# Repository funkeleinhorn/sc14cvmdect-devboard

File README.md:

# SC14CVMDECT Devboard

Open Hardware devboard for the [SC14CVMDECT](https://www.renesas.com/en/products/wireless-connectivity/dect/sc14cvmdect-cordless-voice-module) module from Renesas.
Documentation of the devboard and the existing Open Source Software implementations for the SC14CVMDECT module can be found at [redected.org](https://redected.org).

This project is licensed as open hardware. See LICENSE.txt for details.

## Images

Here you can see how the PCB looks:

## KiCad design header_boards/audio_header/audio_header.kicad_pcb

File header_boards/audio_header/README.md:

# SC14CVMDECT Devboard Audio Header

Header board providing audio circutry for the Open Hardware devboard for the [SC14CVMDECT](https://www.renesas.com/en/products/wireless-connectivity/dect/sc14cvmdect-cordless-voice-module) module from Renesas.
Documentation of the devboard and the header boards can be found at [redected.org](https://redected.org).

This project is licensed as open hardware. See LICENSE.txt for details.

## Images

Here you can see how the PCB looks:

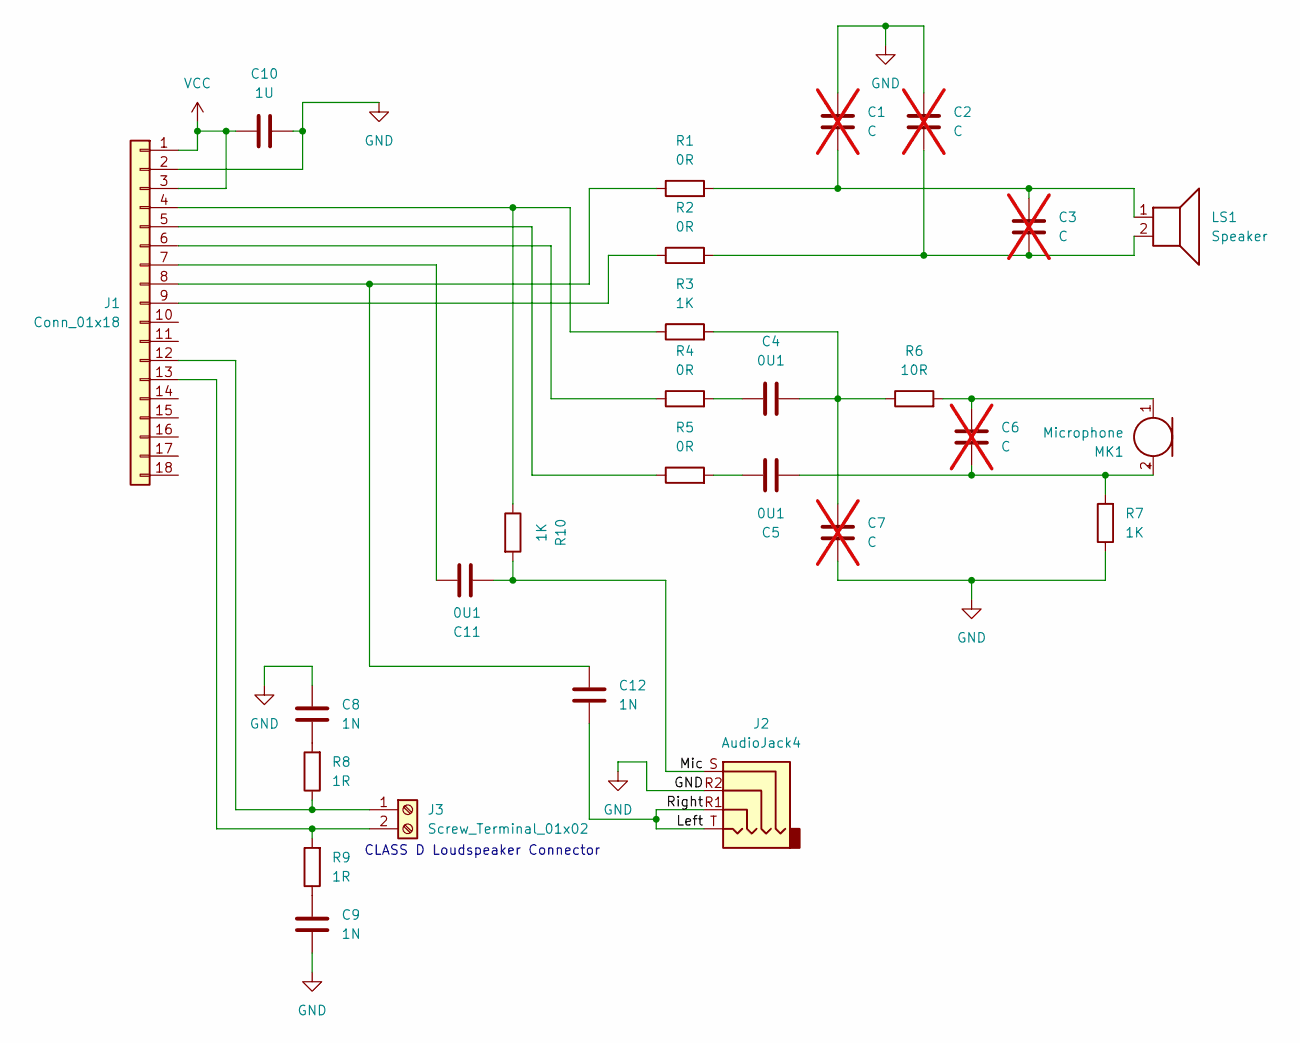
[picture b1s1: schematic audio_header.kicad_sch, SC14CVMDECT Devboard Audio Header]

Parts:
C1, C2, C3, C6, C7: C; C_0603_1608Metric; not fitted
C4, C5, C11: 0U1; C_0603_1608Metric
C8, C9, C12: 1N; C_0603_1608Metric
C10: 1U; C_0603_1608Metric
J1: Conn_01x18; PinSocket_1x18_P2.54mm_Vertical
J2: AudioJack4; Jack_3.5mm_CUI_SJ-4351X-SMT_Horizontal
J3: Screw_Terminal_01x02; TerminalBlock_MaiXu_MX126-5.0-02P_1x02_P5.00mm
LS1: Speaker; Speaker_CUI_CMR-15062S-67
MK1: Microphone; CUI_CMC-4013-SMT
R1, R2, R4, R5: 0R; R_0603_1608Metric
R3, R7, R10: 1K; R_0603_1608Metric
R6: 10R; R_0603_1608Metric
R8, R9: 1R; R_0603_1608Metric

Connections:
/Left: C12.1, J2.R1, J2.T
/Mic: C11.2, J2.S, R10.2
GND: C1.1, C2.1, C7.2, C8.2, C9.1, C10.2, J1.2, J2.R2, R7.1
unnamed: C1.2, C3.1, LS1.1, R1.2
unnamed: C2.2, C3.2, LS1.2, R2.2
unnamed: C4.1, R4.2
unnamed: C4.2, C7.1, R3.2, R6.1
unnamed: C5.1, R5.2
unnamed: C8.1, R8.2
unnamed: C9.2, R9.1
unnamed: J1.4, R3.1, R10.1
unnamed: J1.5, R5.1
unnamed: J1.6, R4.1
unnamed: C11.1, J1.7
unnamed: C12.2, J1.8, R1.1
unnamed: J1.9, R2.1
unnamed: J1.12, J3.1, R8.1
unnamed: J1.13, J3.2, R9.2
unnamed: C5.2, C6.2, MK1.2 (+), R7.2
unnamed: C6.1, MK1.1 (-), R6.2
VCC: C10.1, J1.1, J1.3

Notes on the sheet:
CLASS D Loudspeaker Connector

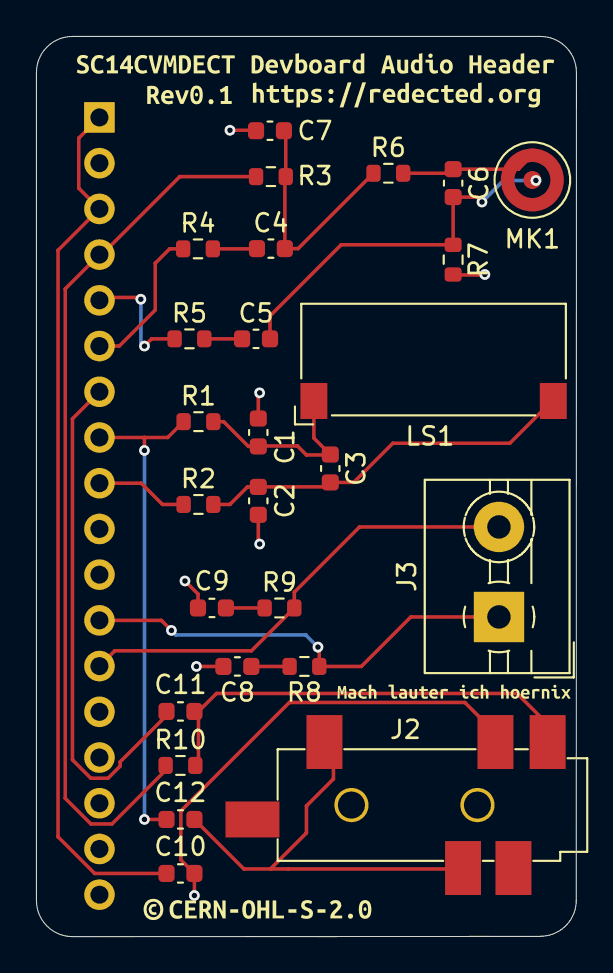
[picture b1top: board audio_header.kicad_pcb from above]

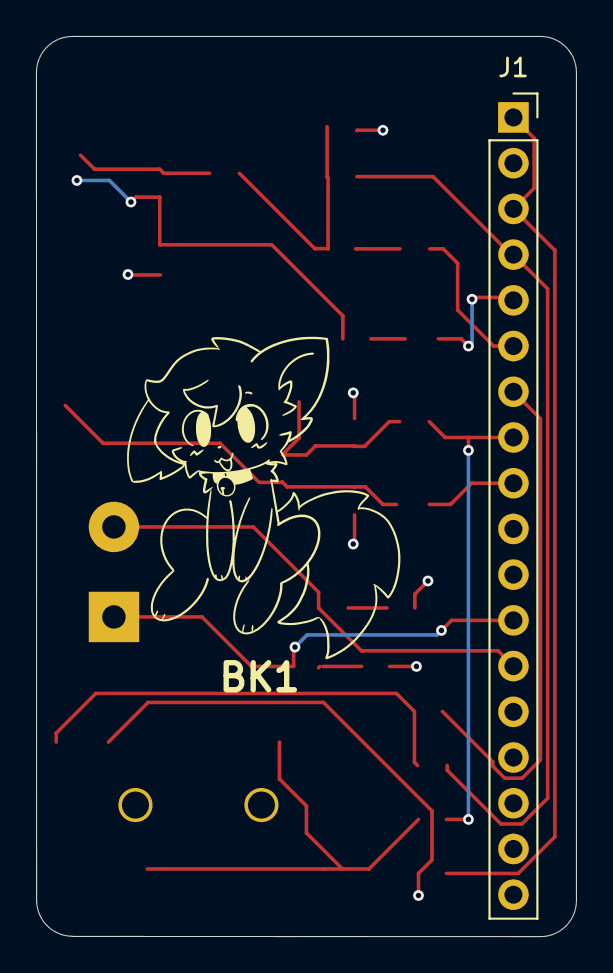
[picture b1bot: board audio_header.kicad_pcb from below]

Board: 4 copper layers, 30.0 x 50.0 mm, 34 parts (2 on the bottom side), 21 nets.

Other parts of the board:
BK1: LOGO
kibuzzard-67A72E30: G***; kibuzzard-67A72E30
kibuzzard-67A72F6B: G***; kibuzzard-67A72F6B
kibuzzard-67A72F64: G***; kibuzzard-67A72F64
kibuzzard-67A72F83: G***; kibuzzard-67A72F83
kibuzzard-67A7302E: G***; kibuzzard-67A7302E
kibuzzard-67ACE384: G***; kibuzzard-67ACE384

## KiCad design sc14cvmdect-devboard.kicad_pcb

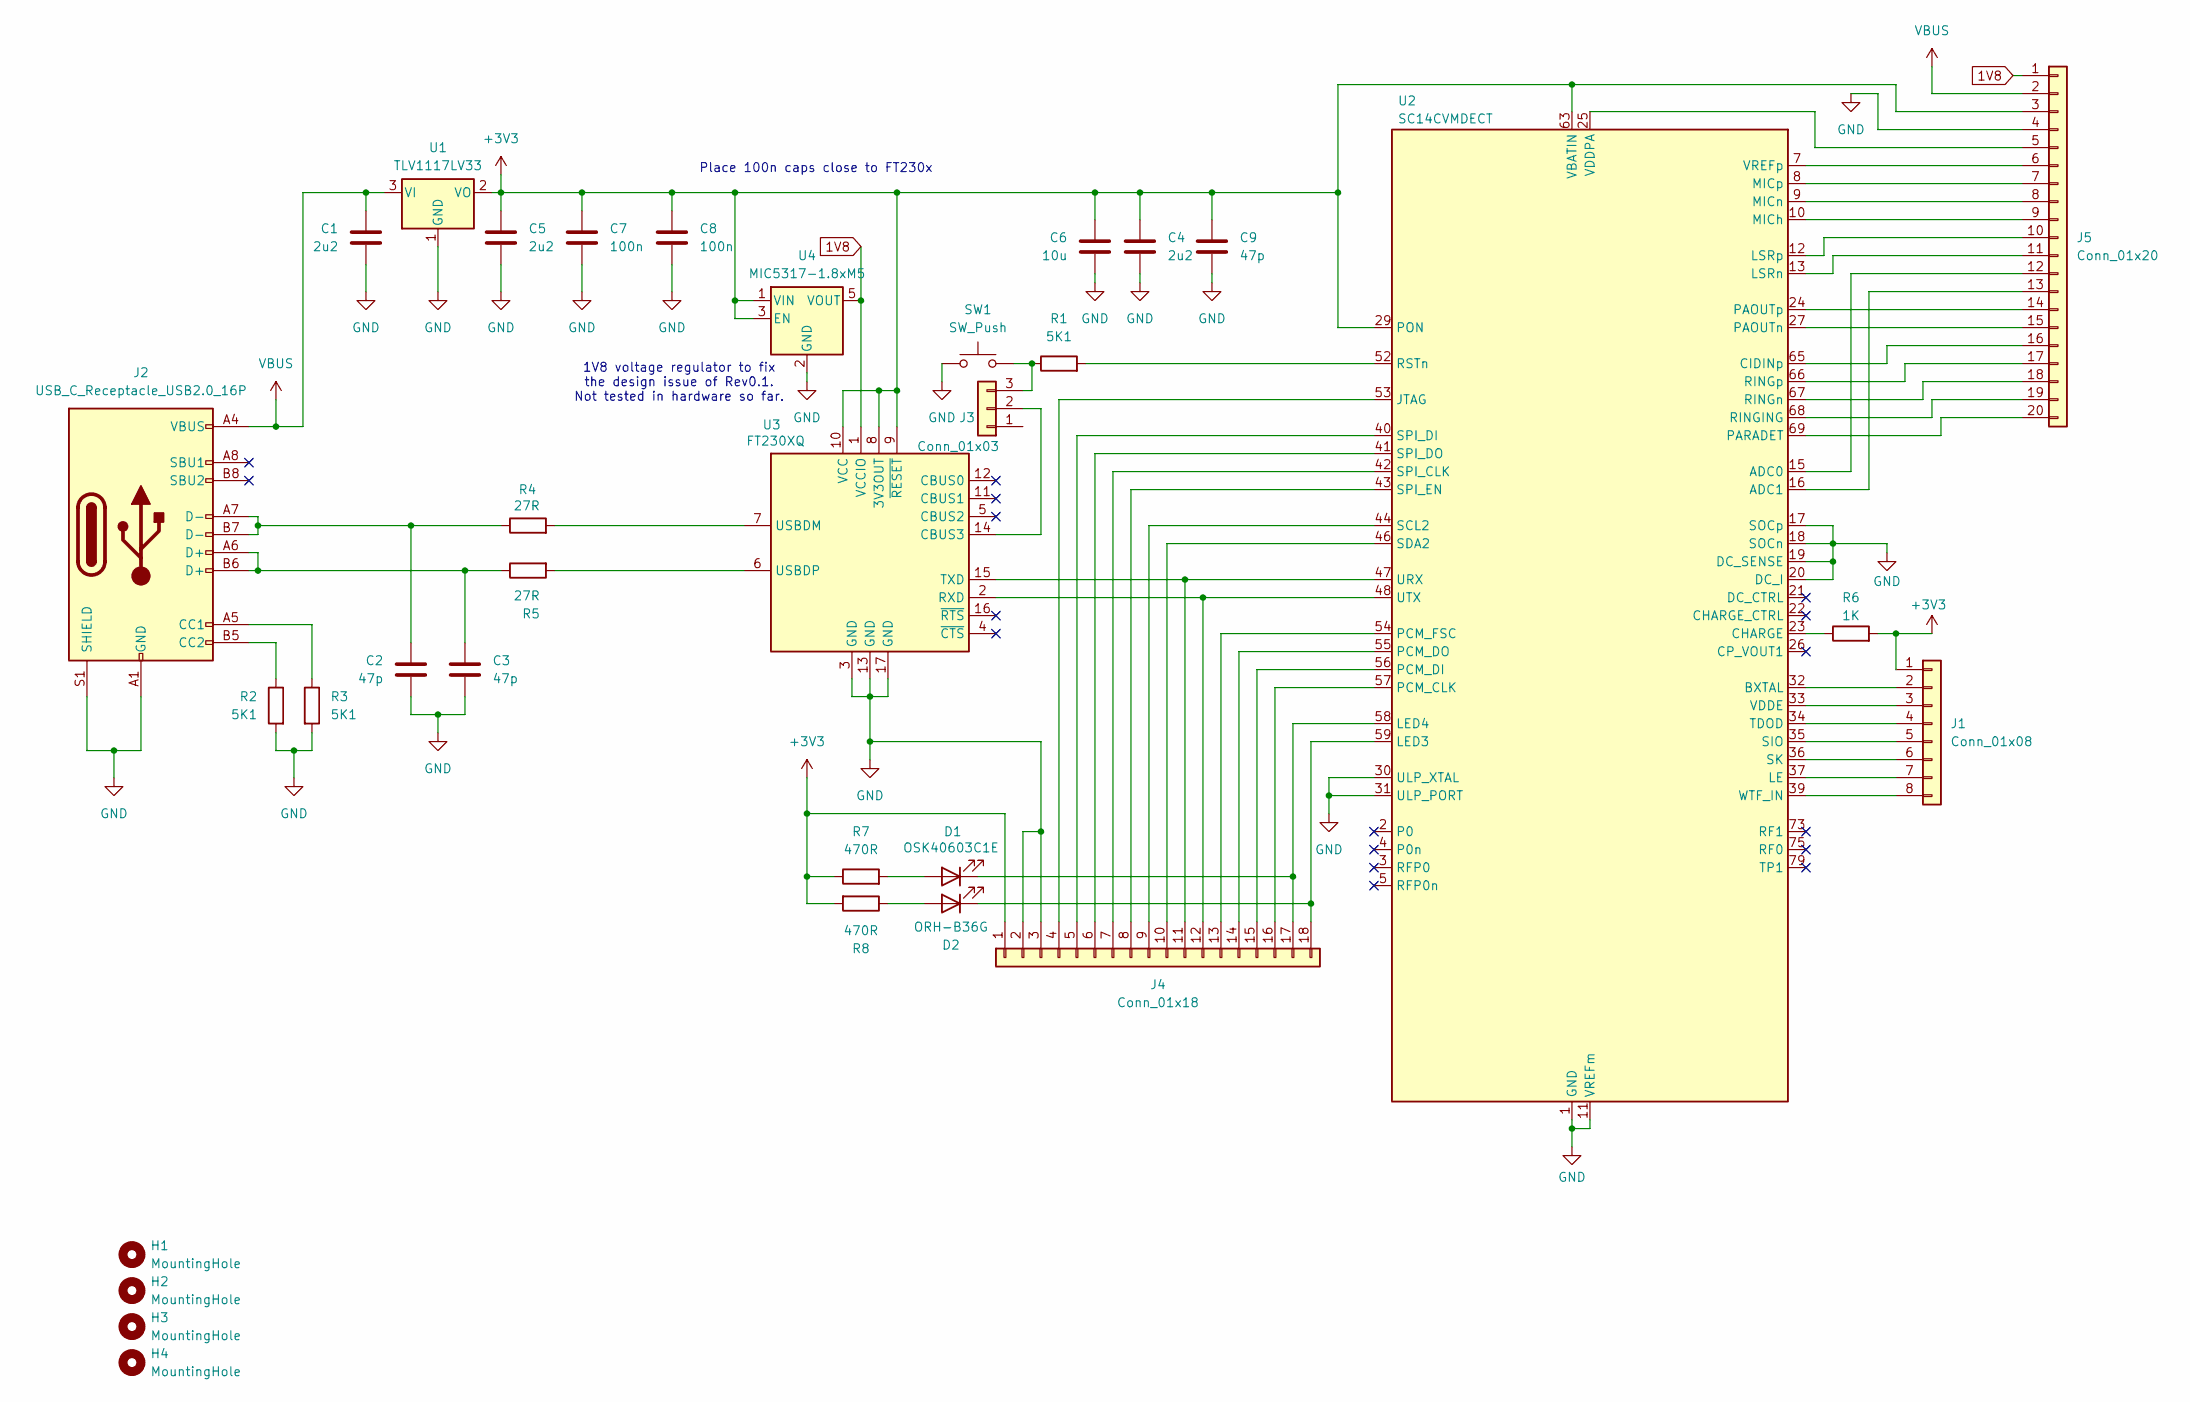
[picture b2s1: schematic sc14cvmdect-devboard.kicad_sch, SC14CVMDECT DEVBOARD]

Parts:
C1, C4, C5: 2u2; C_0805_2012Metric
C2, C3, C9: 47p; C_0603_1608Metric
C6: 10u; C_0805_2012Metric
C7, C8: 100n; C_0603_1608Metric
D1: OSK40603C1E; LED_0603_1608Metric
D2: ORH-B36G; LED_0603_1608Metric
H1, H2, H3, H4: MountingHole; MountingHole_3.2mm_M3_DIN965
J1: Conn_01x08; PinHeader_1x08_P2.54mm_Vertical
J2: USB_C_Receptacle_USB2.0_16P; USB_C_Receptacle_JAE_DX07S016JA1R1500
J3: Conn_01x03; PinHeader_1x03_P2.54mm_Vertical
J4: Conn_01x18; PinHeader_1x18_P2.54mm_Vertical
J5: Conn_01x20; PinHeader_1x20_P2.54mm_Vertical
R1, R2, R3: 5K1; R_0603_1608Metric
R4, R5: 27R; R_0603_1608Metric
R6: 1K; R_0603_1608Metric
R7, R8: 470R; R_0603_1608Metric
SW1: SW_Push; SW_SPST_PTS647_Sx70
U1: TLV1117LV33; SOT-223-3_TabPin2
U2: SC14CVMDECT
U3: FT230XQ; QFN-16-1EP_4x4mm_P0.65mm_EP2.1x2.1mm
U4: MIC5317-1.8xM5; SOT-23-5

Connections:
1V8: J5.1, U3.1 (VCCIO), U4.5 (VOUT)
+3V3: C4.1, C5.1, C6.1, C7.1, C8.1, C9.1, J1.1, J4.1, J5.3, R6.2, R7.1, R8.2, U1.2 (VO), U2.29 (PON), U2.63 (VBATIN), U2.64 (VBATIN), U3.8 (3V3OUT), U3.9 (~RESET), U3.10 (VCC), U4.1 (VIN), U4.3 (EN)
GND: C1.2, C2.2, C3.2, C4.2, C5.2, C6.2, C7.2, C8.2, C9.2, J2.A1 (GND), J2.A12 (GND), J2.B1 (GND), J2.B12 (GND), J2.S1 (SHIELD), J4.2, J4.3, J5.4, R2.2, R3.2, SW1.1, U1.1 (GND), U2.1 (GND), U2.6 (GND), U2.11 (VREFm), U2.14 (GND), U2.17 (SOCp), U2.18 (SOCn), U2.19 (DC_SENSE), U2.20 (DC_I), U2.28 (GND), U2.30 (ULP_XTAL), U2.31 (ULP_PORT), U2.38 (GND), U2.45 (GND), U2.49 (GND), U2.50 (GND), U2.51 (GND), U2.60 (GND), U2.70 (GND), U2.71 (GND), U2.72 (GND), U2.74 (GND), U2.76 (GND), U2.77 (GND), U2.78 (GND), U2.80 (GND), U3.3 (GND), U3.13 (GND), U3.17 (GND), U4.2 (GND)
unnamed: C2.1, J2.A7 (D-), J2.B7 (D-), R4.1
unnamed: C3.1, J2.A6 (D+), J2.B6 (D+), R5.1
unnamed: D1.2 (A), R7.2
unnamed: D1.1 (K), J4.17, U2.58 (LED4)
unnamed: D2.2 (A), R8.1
unnamed: D2.1 (K), J4.18, U2.59 (LED3)
unnamed: J1.2, U2.32 (BXTAL)
unnamed: J1.3, U2.33 (VDDE)
unnamed: J1.4, U2.34 (TDOD)
unnamed: J1.5, U2.35 (SIO)
unnamed: J1.6, U2.36 (SK)
unnamed: J1.7, U2.37 (LE)
unnamed: J1.8, U2.39 (WTF_IN)
unnamed: J2.A5 (CC1), R3.1
unnamed: J2.B5 (CC2), R2.1
unnamed: J3.2, U3.14 (CBUS3)
unnamed: J3.3, R1.1, SW1.2
unnamed: J4.4, U2.53 (JTAG)
unnamed: J4.5, U2.40 (SPI_DI)
unnamed: J4.6, U2.41 (SPI_DO)
unnamed: J4.7, U2.42 (SPI_CLK)
unnamed: J4.8, U2.43 (SPI_EN)
unnamed: J4.9, U2.44 (SCL2)
unnamed: J4.10, U2.46 (SDA2)
unnamed: J4.11, U2.47 (URX), U3.15 (TXD)
unnamed: J4.12, U2.48 (UTX), U3.2 (RXD)
unnamed: J4.13, U2.54 (PCM_FSC)
unnamed: J4.14, U2.55 (PCM_DO)
unnamed: J4.15, U2.56 (PCM_DI)
unnamed: J4.16, U2.57 (PCM_CLK)
unnamed: J5.5, U2.25 (VDDPA)
unnamed: J5.6, U2.7 (VREFp)
unnamed: J5.7, U2.8 (MICp)
unnamed: J5.8, U2.9 (MICn)
unnamed: J5.9, U2.10 (MICh)
unnamed: J5.10, U2.12 (LSRp)
unnamed: J5.11, U2.13 (LSRn)
unnamed: J5.12, U2.15 (ADC0)
unnamed: J5.13, U2.16 (ADC1)
unnamed: J5.14, U2.24 (PAOUTp)
unnamed: J5.15, U2.27 (PAOUTn)
unnamed: J5.16, U2.65 (CIDINp)
unnamed: J5.17, U2.66 (RINGp)
unnamed: J5.18, U2.67 (RINGn)
unnamed: J5.19, U2.68 (RINGING)
unnamed: J5.20, U2.69 (PARADET)
unnamed: R6.1, U2.23 (CHARGE)
unnamed: R1.2, U2.52 (RSTn)
unnamed: R4.2, U3.7 (USBDM)
unnamed: R5.2, U3.6 (USBDP)
VBUS: C1.1, J2.A4 (VBUS), J2.A9 (VBUS), J2.B4 (VBUS), J2.B9 (VBUS), J5.2, U1.3 (VI)

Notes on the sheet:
Place 100n caps close to FT230x
1V8 voltage regulator to fix the design issue of Rev0.1. Not tested in hardware so far.

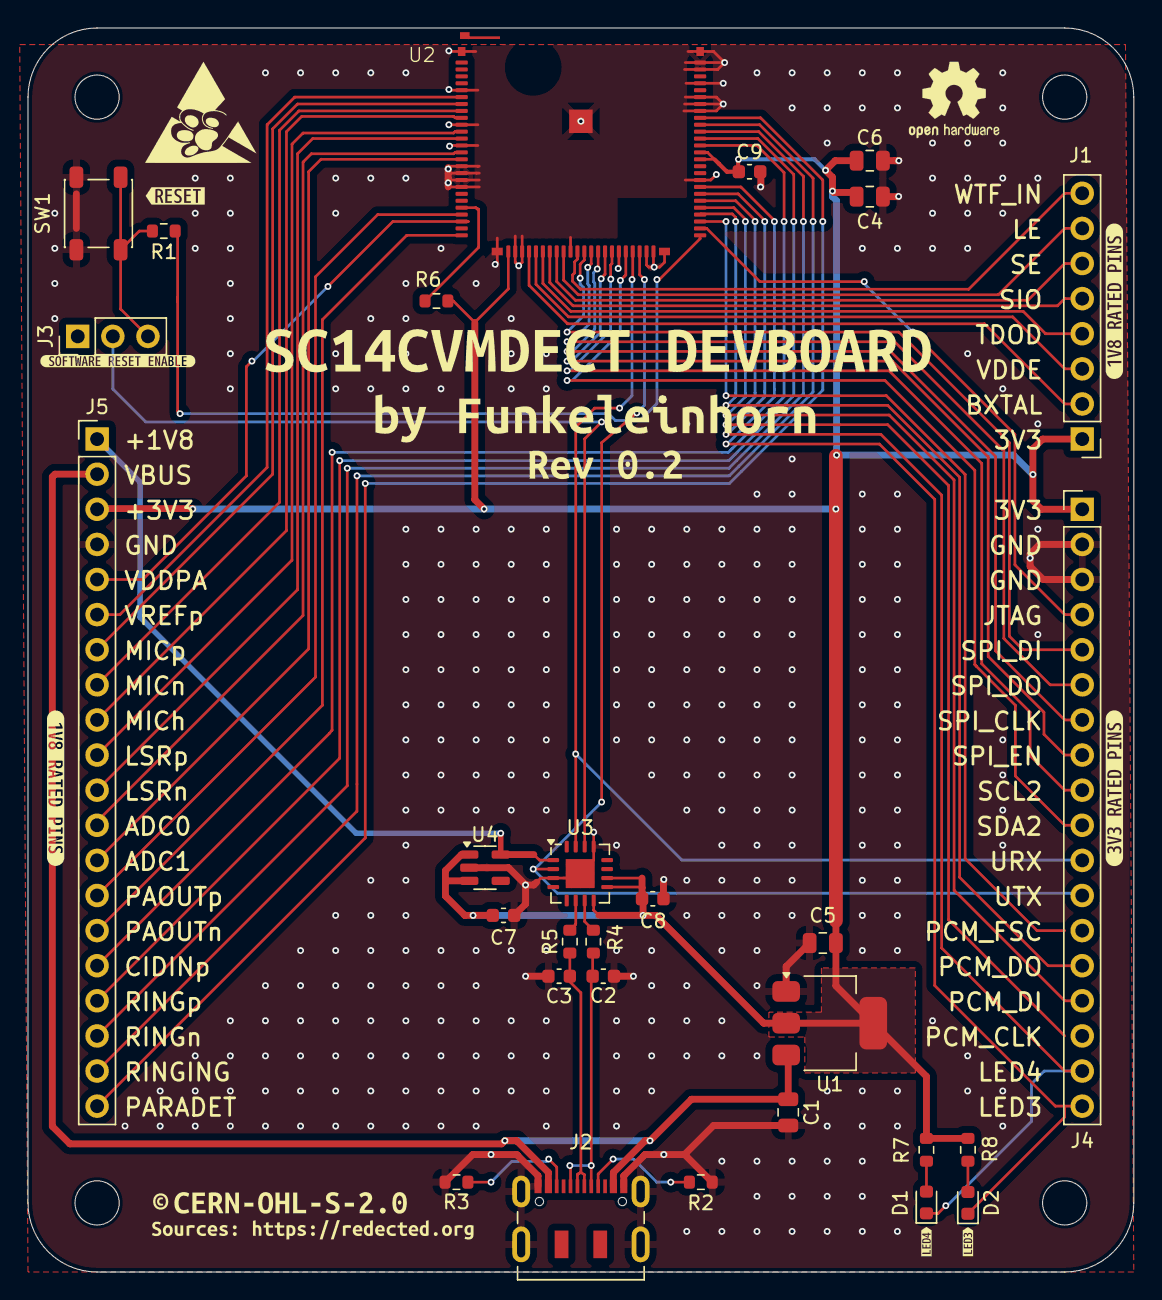
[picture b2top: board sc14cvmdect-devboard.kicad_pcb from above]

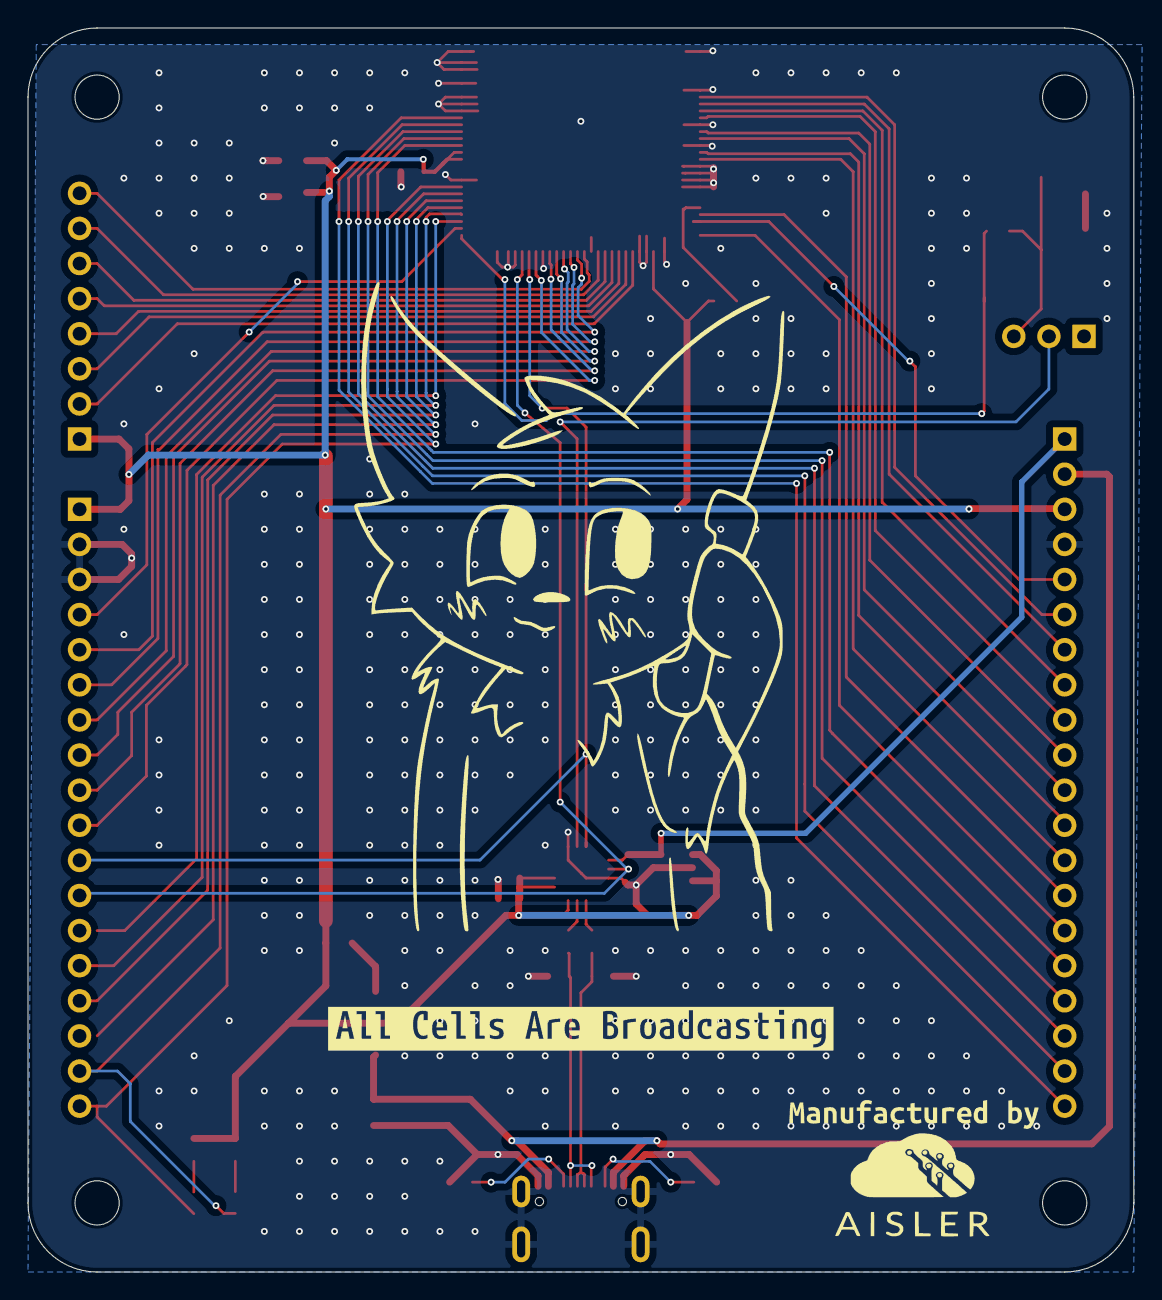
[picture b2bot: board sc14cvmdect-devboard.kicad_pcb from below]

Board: 4 copper layers, 80.0 x 90.0 mm, 48 parts (2 on the bottom side), 54 nets.

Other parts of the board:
kibuzzard-676BF11C: G***; kibuzzard-676BF11C
kibuzzard-67575DB5: G***; kibuzzard-67575DB5
kibuzzard-67575EB8: G***; kibuzzard-67575EB8
kibuzzard-67575F62: G***; kibuzzard-67575F62
kibuzzard-67575F78: G***; kibuzzard-67575F78
kibuzzard-67576AD7: G***; kibuzzard-67576AD7
kibuzzard-67576C4F: G***; kibuzzard-67576C4F
kibuzzard-67576C6D: G***; kibuzzard-67576C6D
kibuzzard-67576C73: G***; kibuzzard-67576C73
kibuzzard-67576CB2: G***; kibuzzard-67576CB2
kibuzzard-675753CF: G***; kibuzzard-675753CF
kibuzzard-675756D3: G***; kibuzzard-675756D3
kibuzzard-675758CB: G***; kibuzzard-675758CB
kibuzzard-67575390: G***; kibuzzard-67575390
kibuzzard-67575747: G***; kibuzzard-67575747

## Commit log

2024-12-20 Revision 0.1
    The initial revision of the SC14CVMDECT devboard.
    15 boards of this revision were manufactured for and handed out at 38C3.
2024-12-24 Add badges to README
2024-12-25 Add 1V8 voltage regulator to fix internal UART voltage.
    This commits adds a voltage regulator to change the voltage at the
    VCCIO pin of the internal UART converter to 1V8.
    This design was not tested in production/hardware yet but instead
    is a hot fix to offer an alternative to the manufacturing of boards
    with the wrong UART voltage.
2025-01-17 tweaks
    Added
    - +1V8 on left pinheader
    - VBUS on left pinheader
    Moved RESET Button up a little
    Moved Jumper up a little
    Moved right pinheaders by 1.27mm so they match a standard raster
2025-01-22 ci/cd: Add pdf auto rendering github action
2025-01-22 chore: update schematic PDF [skip ci]
2025-01-22 rename branch references to master to main
2025-04-18 add audio header board
